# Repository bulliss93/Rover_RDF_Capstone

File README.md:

# Rover_RDF_Capstone
Repository for the 2022-2023 Mars Rover RDF Capstone Project

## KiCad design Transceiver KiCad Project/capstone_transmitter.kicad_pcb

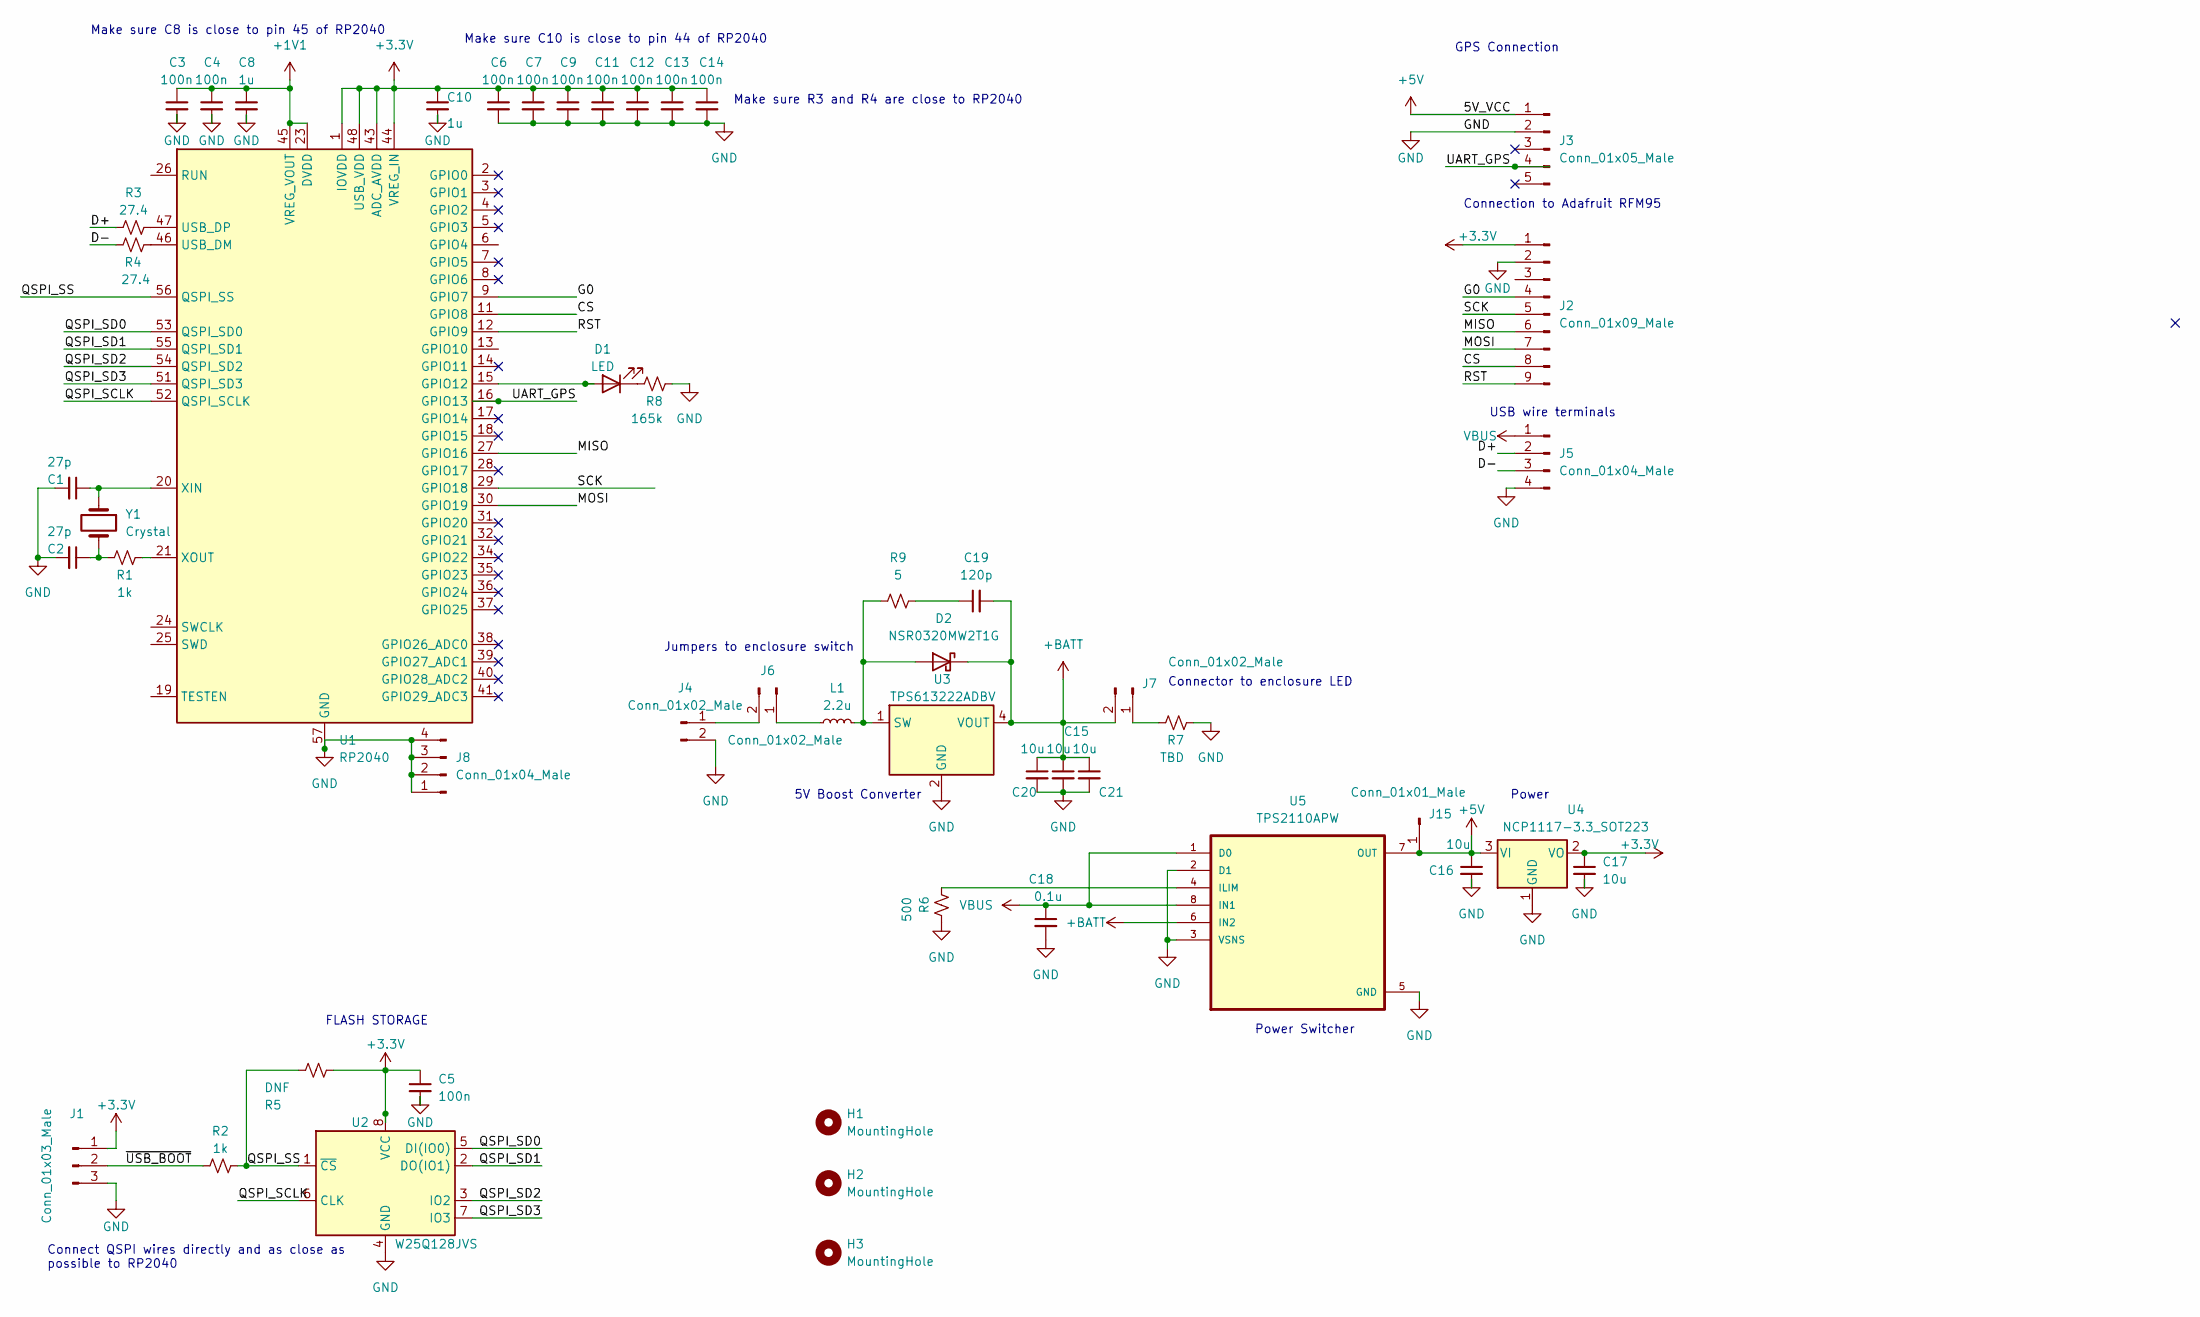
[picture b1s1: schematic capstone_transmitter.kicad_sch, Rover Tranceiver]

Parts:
C1, C2: 27p; C_0603_1608Metric_Pad1.08x0.95mm_HandSolder; Digi-Key_PN 490-8067-1-ND
C3, C4, C5, C6, C7, C9, C11, C12, C13, C14: 100n; C_0603_1608Metric_Pad1.08x0.95mm_HandSolder; Digi-Key_PN 490-12232-1-ND
C8, C10: 1u; C_0603_1608Metric_Pad1.08x0.95mm_HandSolder; Digi-Key_PN 490-7229-1-ND
C15, C20, C21: 10u; C_0603_1608Metric_Pad1.08x0.95mm_HandSolder; Digi-Key_PN 490-12232-1-ND
C16, C17: 10u; C_0603_1608Metric_Pad1.08x0.95mm_HandSolder; Digi-Key_PN 1276-1119-1-ND
C18: 0.1u; C_0603_1608Metric_Pad1.08x0.95mm_HandSolder; Digi-Key_PN 490-12232-1-ND
C19: 120p; C_0603_1608Metric_Pad1.08x0.95mm_HandSolder
D1: LED; LED_0805_2012Metric
D2: NSR0320MW2T1G; D_SOD-323
H1, H2, H3: MountingHole; MountingHole_2.1mm
J1: Conn_01x03_Male; PinHeader_1x03_P2.54mm_Vertical
J2: Conn_01x09_Male; PinHeader_1x09_P2.54mm_Vertical
J3: Conn_01x05_Male; PinHeader_1x05_P2.54mm_Vertical
J4: Conn_01x02_Male; JST_EH_B2B-EH-A_1x02_P2.50mm_Vertical
J5, J8: Conn_01x04_Male; PinHeader_1x04_P2.54mm_Vertical
J6, J7: Conn_01x02_Male; PinHeader_1x02_P2.54mm_Vertical
J15: Conn_01x01_Male; PinHeader_1x01_P2.54mm_Vertical
L1: 2.2u; L_0402_1005Metric
R1, R2: 1k; R_0603_1608Metric_Pad0.98x0.95mm_HandSolder; Digi-Key_PN RNCP0603FTD1K00CT-ND
R3, R4: 27.4; R_0603_1608Metric_Pad0.98x0.95mm_HandSolder; Digi-Key_PN P27.4HCT-ND
R5: DNF; R_0603_1608Metric_Pad0.98x0.95mm_HandSolder
R6: 500; R_0603_1608Metric_Pad0.98x0.95mm_HandSolder; Digi-Key_PN RNCP0603FTD1K00CT-ND
R7: TBD; R_0603_1608Metric_Pad0.98x0.95mm_HandSolder; Digi-Key_PN RNCP0603FTD1K00CT-ND
R8: 165k; R_0603_1608Metric_Pad0.98x0.95mm_HandSolder; Digi-Key_PN RNCP0603FTD1K00CT-ND
R9: 5; R_0603_1608Metric_Pad0.98x0.95mm_HandSolder
U1: RP2040; QFN-56-1EP_7x7mm_P0.4mm_EP3.2x3.2mm; Part Number 2648-SC0914(7)TR-ND; Digi-Key_PN 2648-SC0914(13)CT-ND
U2: W25Q128JVS; SOIC-8_5.23x5.23mm_P1.27mm; Part Number W25Q128JVSIQ-ND; Digi-Key_PN W25Q128JVSIQCT-ND
U3: TPS613222ADBV; SOT-23-5
U4: NCP1117-3.3_SOT223; SOT-223-3_TabPin2; Part Number NCP1117LPST33T3GOSCT-ND; Digi-Key_PN NCP1117LPST33T3GOSCT-ND
U5: TPS2110APW; SOP65P640X120-8N
Y1: Crystal; Crystal_SMD_HC49-SD; Part Number 535-10218-1-ND; Digi-Key_PN 535-10218-1-ND - Cut Tape

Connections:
+1V1: C3.1, C4.1, C8.1, U1.23 (DVDD), U1.45 (VREG_VOUT), U1.50 (DVDD)
+3.3V: C5.1, C6.1, C7.1, C9.1, C10.1, C11.1, C12.1, C13.1, C14.1, C17.1, J1.1, J2.1, R5.1, U1.1 (IOVDD), U1.10 (IOVDD), U1.22 (IOVDD), U1.33 (IOVDD), U1.42 (IOVDD), U1.43 (ADC_AVDD), U1.44 (VREG_IN), U1.48 (USB_VDD), U1.49 (IOVDD), U2.8 (VCC), U4.2 (VO)
+5V: C16.1, J3.1, J15.1, U4.3 (VI), U5.7 (OUT)
+BATT: C15.1, C19.2, C20.1, C21.1, D2.1 (K), J7.2, U3.4 (VOUT), U5.6 (IN2)
/CS: J2.8, U1.11 (GPIO8)
/D+: J5.2, R3.1
/D-: J5.3, R4.1
/G0: J2.4, U1.9 (GPIO7)
/MISO: J2.6, U1.27 (GPIO16)
/MOSI: J2.7, U1.30 (GPIO19)
/QSPI_SCLK: U1.52 (QSPI_SCLK), U2.6 (CLK)
/QSPI_SD0: U1.53 (QSPI_SD0), U2.5 (DI(IO0))
/QSPI_SD1: U1.55 (QSPI_SD1), U2.2 (DO(IO1))
/QSPI_SD2: U1.54 (QSPI_SD2), U2.3 (IO2)
/QSPI_SD3: U1.51 (QSPI_SD3), U2.7 (IO3)
/QSPI_SS: R2.1, R5.2, U1.56 (QSPI_SS), U2.1 (~CS)
/RST: J2.9, U1.12 (GPIO9)
/SCK: J2.5, U1.29 (GPIO18)
/UART_GPS: J3.4, U1.16 (GPIO13)
/~USB_BOOT: J1.2, R2.2
GND: C1.2, C2.2, C3.2, C4.2, C5.2, C6.2, C7.2, C8.2, C9.2, C10.2, C11.2, C12.2, C13.2, C14.2, C15.2, C16.2, C17.2, C18.2, C20.2, C21.2, J1.3, J2.2, J3.2, J4.2, J5.4, J8.1, J8.2, J8.3, J8.4, R6.2, R7.2, R8.2, U1.57 (GND), U2.4 (GND), U3.2 (GND), U4.1 (GND), U5.2 (D1), U5.3 (VSNS), U5.5 (GND)
unnamed: C1.1, U1.20 (XIN), Y1.1
unnamed: C2.1, R1.2, Y1.2
unnamed: C19.1, R9.1
unnamed: D1.1 (K), R8.1
unnamed: D1.2 (A), U1.15 (GPIO12)
unnamed: D2.2 (A), L1.2, R9.2, U3.1 (SW)
unnamed: J4.1, J6.2
unnamed: J6.1, L1.1
unnamed: J7.1, R7.1
unnamed: R1.1, U1.21 (XOUT)
unnamed: R3.2, U1.47 (USB_DP)
unnamed: R4.2, U1.46 (USB_DM)
unnamed: R6.1, U5.4 (ILIM)
VBUS: C18.1, J5.1, U5.1 (D0), U5.8 (IN1)

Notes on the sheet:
Connect QSPI wires directly and as close as possible to RP2040
Power
Make sure R3 and R4 are close to RP2040
5V Boost Converter
USB wire terminals
Connector to enclosure LED
Make sure C8 is close to pin 45 of RP2040
Jumpers to enclosure switch
Power Switcher
GPS Connection
Connection to Adafruit RFM95
Make sure C10 is close to pin 44 of RP2040
FLASH STORAGE

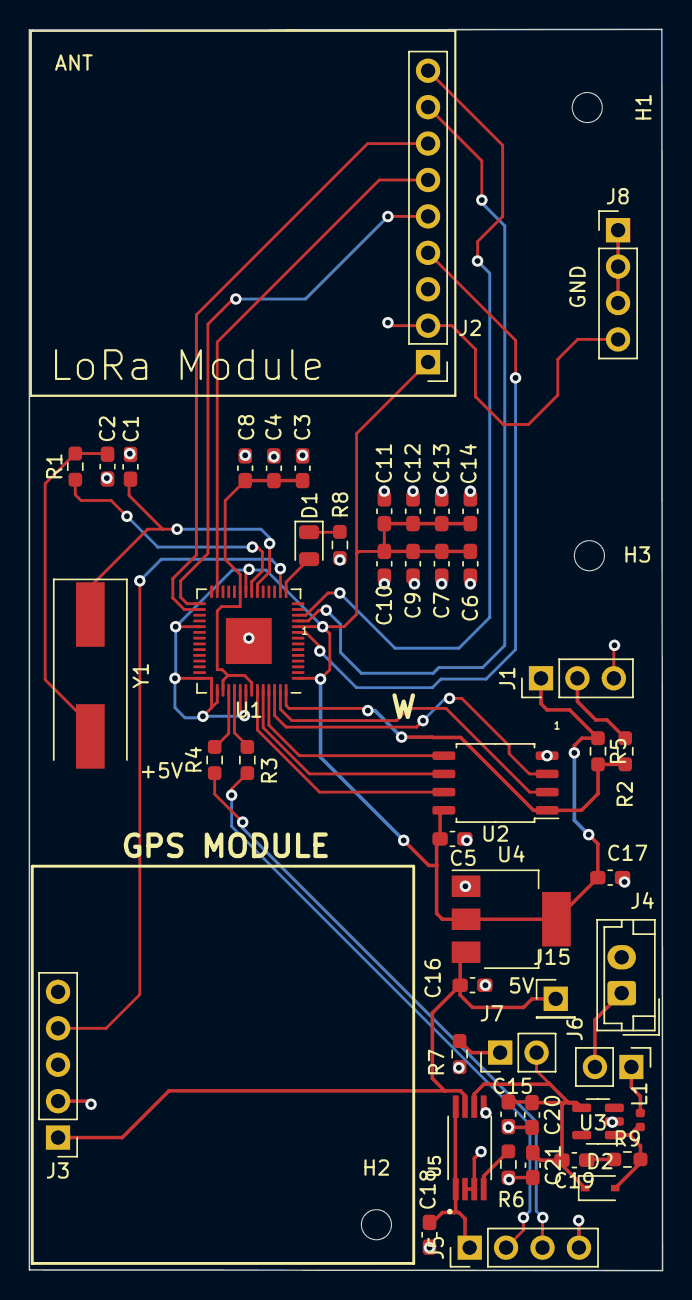
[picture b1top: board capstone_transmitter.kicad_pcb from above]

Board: 2 copper layers, 44.2 x 86.5 mm, 51 parts (0 on the bottom side), 35 nets.

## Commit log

2023-04-29 Upload of the mostup to date code for the tracking algorithm and UI (minus changes to integrate the UI into the existing groundstation)
2023-05-02 Add files via upload
    transmitter files
2023-05-02 transmitter files
2023-05-02 transceiver design files
